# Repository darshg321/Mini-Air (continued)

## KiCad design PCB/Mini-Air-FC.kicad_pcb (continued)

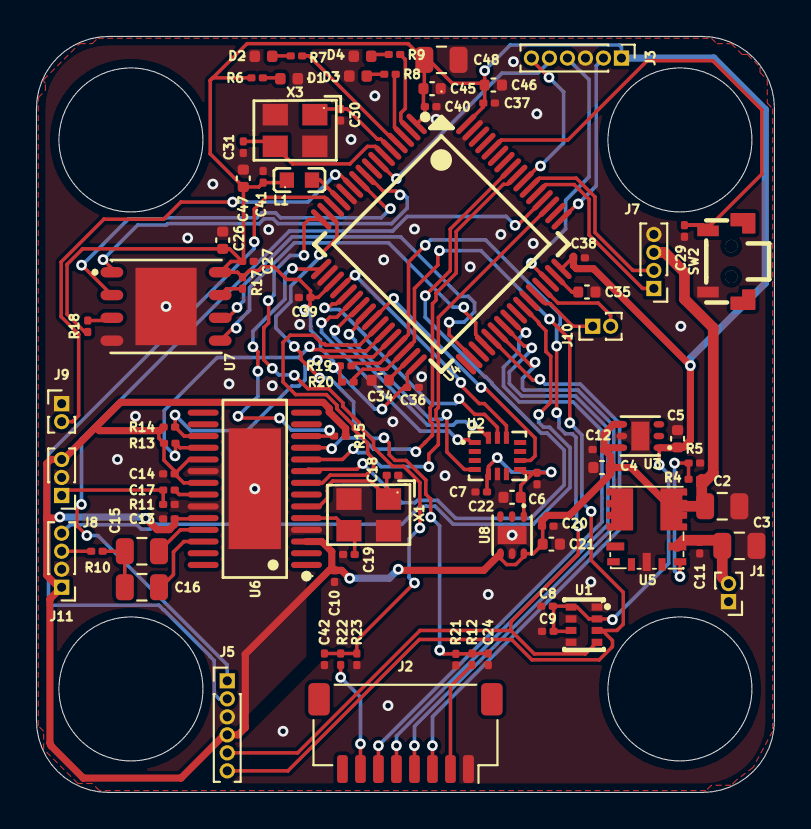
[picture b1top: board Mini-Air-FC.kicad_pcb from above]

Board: 2 copper layers, 41.0 x 42.0 mm, 84 parts (0 on the bottom side), 68 nets.

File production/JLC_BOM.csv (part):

"JLCPCB BOM Tool - BOM Matching","","","","","","","","","","","","","","","","",""
"BOM name：production_bom-JLCPCB Assembly Order.xlsx","","","Download Time：2026-06-21 03:50:59","","","","* Our matching results are updated in real-time, but stock and prices may change. 
If it's been over 24 hours, please re-match before placing your order.","","","","","","","","","",""
"PCB Assembled Qty：5","","","Est. Total Price：83.5555","","","","","","","","","","","","","",""
"Your BOM","","","","","Matched Parts","","","","","","","Order Information","","","","",""
"Top Designator","Bottom Designator","Comment","Footprint","JLCPCB Part #","Matches","Part # ","Manufacturer","Footprint","Description","Category","Warning","JLCPCB Part #","Product link","Lib Type","Qty","Source","Total Price ($)"
"C10,C11,C12,C13,C14,C17,C21,C24,C27,C29,C36,C37,C38,C39,C40,C41,C42,C6,C7,C8,C9","","100nF","0201","","Select by Customer","GRM033R61E104KE14D","Murata Electronics","0201","100nF 25V X5R ±10% 0201 Multilayer Ceramic Capacitors MLCC - SMD/SMT ROHS","Multilayer Ceramic Capacitors MLCC - SMD/SMT","","C76939","https://jlcpcb.com/partdetail/MurataElectronics-GRM033R61E10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","Extended","54","54 JLCPCB","0.6102"
"C15,C16,C2,C3","","22uF","0805","","Select by System","CL21A226MAQNNNE","Samsung Electro-Mechanics","0805","22uF 25V X5R ±20% 0805 Multilayer Ceramic Capacitors MLCC - SMD/SMT ROHS","Multilayer Ceramic Capacitors MLCC - SMD/SMT","","C45783","https://jlcpcb.com/partdetail/46786-CL21A226MAQNNNE/C45783","Basic","16","16 JLCPCB","1.8784"
"C18,C19","","22pF","0201","","Select by Customer","GRM0335C1H220JA01D","Murata Electronics","0201","22pF 50V C0G ±5% 0201 Multilayer Ceramic Capacitors MLCC - SMD/SMT ROHS","Multilayer Ceramic Capacitors MLCC - SMD/SMT","","C76924","https://jlcpcb.com/partdetail/MurataElectronics-GRM0335C1H22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","Extended","20","20 JLCPCB","0.066"
"C20,C22,C26,C4,C45,C46,C47,C5","","1uF","0402","","Select by System","CL05A105KA5NQNC","Samsung Electro-Mechanics","0402","1uF 25V X5R ±10% 0402 Multilayer Ceramic Capacitors MLCC - SMD/SMT ROHS","Multilayer Ceramic Capacitors MLCC - SMD/SMT","","C52923","https://jlcpcb.com/partdetail/53938-CL05A105KA5NQNC/C52923","Basic","26","26 JLCPCB","0.4056"
"C30,C31","","18pF","0201","","Select by System","0201CG180J500NT","FH (Guangdong Fenghua Advanced Tech)","0201","18pF 50V C0G ±5% 0201 Multilayer Ceramic Capacitors MLCC - SMD/SMT ROHS","Multilayer Ceramic Capacitors MLCC - SMD/SMT","","C62164","https://jlcpcb.com/partdetail/63221-0201CG180J500NT/C62164","Extended","20","20 JLCPCB","0.028"
"C34,C35","","2.2uF","0402","","Select by Customer","GRM155R61E225ME15D","Murata Electronics","0402","2.2uF 25V X5R ±20% 0402 Multilayer Ceramic Capacitors MLCC - SMD/SMT ROHS","Multilayer Ceramic Capacitors MLCC - SMD/SMT","","C72203","https://jlcpcb.com/partdetail/MurataElectronics-GRM155R61E22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","Extended","8","8 JLCPCB","0.3792"
"C48","","10uF","0805","","Select by System","GRM21BR61H106KE43L","Murata Electronics","0805","10uF 50V X5R ±10% 0805 Multilayer Ceramic Capacitors MLCC - SMD/SMT ROHS","Multilayer Ceramic Capacitors MLCC - SMD/SMT","","C440198","https://jlcpcb.com/partdetail/439567-GRM21BR61H106KE43L/C440198","Basic","5","5 JLCPCB","1.053"
"D1,D2,D3,D4","","LED","0402","","Select by Customer","XL-1005UGC","XINGLIGHT","0402","-40℃~+85℃ 120° 249mcd 25mA 3V 516nm~531nm 531nm 80mW Discrete Diode Emerald Green Top-mount Water Clear 0402 LED Indication - Discrete ROHS","LED Indication - Discrete","1.The comment (XL-1005UGC) of this part does not match the one (LED) provided in your BOM. Please confirm;","C965793","https://jlcpcb.com/partdetail/XINGLIGHT-XL1005UGC/C965793","Extended","20","20 JLCPCB","0.16"
"L1","","FCM1608KF-601T03","L0603","","Select by System","FCM1608KF-601T03","TAI-TECH","0603","-55℃~+125℃ 1 350mA 500mΩ 600Ω@100MHz ±25% 0603 Ferrite Beads ROHS","Ferrite Beads","","C141723","https://jlcpcb.com/partdetail/TAITECH-FCM1608KF601T03/C141723","Extended","20","20 JLCPCB","0.202"
"R5","","1.37K","0201","","Select by Customer","RTT011371FTH","RALEC","0201","-55℃~+125℃ 1.37kΩ 25V 50mW Thick Film Resistor ±1% ±200ppm/℃ 0201 Chip Resistor - Surface Mount ROHS","Chip Resistor - Surface Mount","1.The comment (RTT011371FTH) of this part does not match the one (1.37K) provided in your BOM. Please confirm;","C166356","https://jlcpcb.com/partdetail/RALEC-RTT011371FTH/C166356","Extended","20","20 JLCPCB","0.028"
"R6,R7,R8,R9","","500","0201","","Select by Customer","RC0201FR-07499RL","YAGEO","0201","-55℃~+125℃ 25V 499Ω 50mW Thick Film Resistor ±1% ±200ppm/℃ 0201 Chip Resistor - Surface Mount ROHS","Chip Resistor - Surface Mount","1.The comment (RC0201FR-07499RL) of this part does not match the one (500) provided in your BOM. Please confirm;","C138137","https://jlcpcb.com/partdetail/YAGEO-RC0201FR07499RL/C138137","Extended","20","20 JLCPCB","0.022"
"R10,R11","","75","0201","","Select by Customer","AC0201FR-0775RL","YAGEO","0201","-55℃~+155℃ 25V 50mW 75Ω Thick Film Resistor ±1% ±200ppm/℃ 0201 Chip Resistor - Surface Mount ROHS","Chip Resistor - Surface Mount","1.The comment (AC0201FR-0775RL) of this part does not match the one (75) provided in your BOM. Please confirm;","C226616","https://jlcpcb.com/partdetail/YAGEO-AC0201FR0775RL/C226616","Extended","20","20 JLCPCB","0.04"
"R12,R22","","100K","0201","","Select by Customer","RTT011003FTH","RALEC","0201","-55℃~+125℃ 100kΩ 25V 50mW Thick Film Resistor ±1% ±200ppm/℃ 0201 Chip Resistor - Surface Mount ROHS","Chip Resistor - Surface Mount","1.The comment (RTT011003FTH) of this part does not match the one (100K) provided in your BOM. Please confirm;","C102685","https://jlcpcb.com/partdetail/RALEC-RTT011003FTH/C102685","Extended","20","20 JLCPCB","0.02"
"R13,R14,R15","","1K","0201","","Select by Customer","RC0201FR-071KL","YAGEO","0201","-55℃~+125℃ 1kΩ 25V 50mW Thick Film Resistor ±1% ±200ppm/℃ 0201 Chip Resistor - Surface Mount ROHS","Chip Resistor - Surface Mount","1.The comment (RC0201FR-071KL) of this part does not match the one (1K) provided in your BOM. Please confirm;","C138165","https://jlcpcb.com/partdetail/YAGEO-RC0201FR071KL/C138165","Extended","20","20 JLCPCB","0.022"
"R17,R18,R19,R20,R4","","10K","0201","","Select by Customer","RC0201JR-0710KL","YAGEO","0201","-55℃~+125℃ 10kΩ 25V 50mW Thick Film Resistor ±200ppm/℃ ±5% 0201 Chip Resistor - Surface Mount ROHS","Chip Resistor - Surface Mount","1.The comment (RC0201JR-0710KL) of this part does not match the one (10K) provided in your BOM. Please confirm;","C138117","https://jlcpcb.com/partdetail/YAGEO-RC0201JR0710KL/C138117","Extended","20","20 JLCPCB","0.02"
"R21,R23","","47K","0201","","Select by Customer","RC0201FR-0747KL","YAGEO","0201","-55℃~+125℃ 25V 47kΩ 50mW Thick Film Resistor ±1% ±200ppm/℃ 0201 Chip Resistor - Surface Mount ROHS","Chip Resistor - Surface Mount","1.The comment (RC0201FR-0747KL) of this part does not match the one (47K) provided in your BOM. Please confirm;","C138139","https://jlcpcb.com/partdetail/YAGEO-RC0201FR0747KL/C138139","Extended","20","20 JLCPCB","0.022"
"SW2","","TS24CA","SW-SMD_2P-TS24CA","","Select by System","TS24CA","SHOU HAN","SMD,4.6x1.8mm","-20℃~+70℃ 1.6N 1.9mm 12V 20,000 cycles 3.5mm 4.7mm 50mA Black No Rectangular Button SMD(SMT) Tab SPST Surface Mount, Right Angle Without Bracket SMD,4.6x1.8mm Tactile Switches ROHS","Tactile Switches","","C393942","https://jlcpcb.com/partdetail/SHOUHAN-TS24CA/C393942","Extended","7","7 JLCPCB","0.175"
"U1","","BMP280","LGA-8_L2.5-W2.0-P0.65_AMP6127","","Select by System","BMP280","Bosch Sensortec","LGA-8(2x2.5)","-40℃~+85℃ 0.12hpa 1.5pa/K 1.71V~3.6V 1hpa 300nA 30Kpa~1.1bar I2C、SPI LGA-8(2x2.5) Pressure Sensors ROHS","Pressure Sensors","","C83291","https://jlcpcb.com/partdetail/BoschSensortec-BMP280/C83291","Extended","2","2 JLCPCB","13.7058"
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
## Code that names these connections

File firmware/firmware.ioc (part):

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Mcu.Name=STM32F405RGTx
Mcu.Package=LQFP64
Mcu.UserName=STM32F405RGTx
PA0-WKUP.GPIOParameters=GPIO_Label
PA0-WKUP.GPIO_Label=GPS_RX
PA0-WKUP.Mode=Asynchronous
PA0-WKUP.Signal=UART4_TX
PA1.GPIOParameters=GPIO_Label
PA1.GPIO_Label=ADC_V_ESC
PA1.Signal=ADCx_IN1
PA10.Mode=Asynchronous
PA10.Signal=USART1_RX
PA11.GPIOParameters=GPIO_Label
PA11.GPIO_Label=TEST_OUT
PA11.Signal=GPIO_Output
PA12.GPIOParameters=GPIO_Label
PA12.GPIO_Label=TEST_IN
PA12.Signal=GPIO_Input
PA13.GPIOParameters=GPIO_Label
PA13.GPIO_Label=SWDIO
PA13.Mode=Trace_Asynchronous_SW
PA13.Signal=SYS_JTMS-SWDIO
PA14.GPIOParameters=GPIO_Label
PA14.GPIO_Label=SWCLK
PA14.Mode=Trace_Asynchronous_SW
PA14.Signal=SYS_JTCK-SWCLK
PA2.GPIOParameters=GPIO_Label
PA2.GPIO_Label=ADC_C_ESC
PA2.Signal=ADCx_IN2
PA3.GPIOParameters=GPIO_Label
PA3.GPIO_Label=OSD_LOS
PA3.Signal=GPIO_Input
PA4.GPIOParameters=GPIO_Label
PA4.GPIO_Label=ICM_CS
PA4.Signal=GPIO_Output
PA5.GPIOParameters=GPIO_Label
PA5.GPIO_Label=ICM_SCK
PA5.Mode=Full_Duplex_Master
PA5.Signal=SPI1_SCK
PA6.GPIOParameters=GPIO_Label
PA6.GPIO_Label=ICM_SDO
PA6.Mode=Full_Duplex_Master
PA6.Signal=SPI1_MISO
PA7.GPIOParameters=GPIO_Label
PA7.GPIO_Label=ICM_SDI
PA7.Mode=Full_Duplex_Master
PA7.Signal=SPI1_MOSI
PA9.GPIOParameters=GPIO_Label
PA9.GPIO_Label=VTX_RX
PA9.Mode=Asynchronous
PA9.Signal=USART1_TX
PB0.GPIOParameters=GPIO_Label
PB0.GPIO_Label=OSD_CS
PB0.Signal=GPIO_Output
PB1.GPIOParameters=GPIO_Label
PB1.GPIO_Label=OSD_HSYNC
PB1.Signal=GPIO_Input
PB10.GPIOParameters=GPIO_Label
PB10.GPIO_Label=SCL
PB10.Mode=I2C
PB10.Signal=I2C2_SCL
PB11.GPIOParameters=GPIO_Label
PB11.GPIO_Label=SDA
PB11.Mode=I2C
PB11.Signal=I2C2_SDA
PB13.GPIOParameters=GPIO_Label
PB13.GPIO_Label=MEM_SCK
PB13.Mode=Full_Duplex_Master
PB13.Signal=SPI2_SCK
PB15.GPIOParameters=GPIO_Label
PB15.GPIO_Label=MEM_SDI
PB15.Mode=Full_Duplex_Master
PB15.Signal=SPI2_MOSI
PB2.GPIOParameters=GPIO_Label
PB2.GPIO_Label=OSD_VSYNC
PB2.Signal=GPIO_Input
PB3.GPIOParameters=GPIO_Label
PB3.GPIO_Label=SWO
PB3.Mode=Trace_Asynchronous_SW
PB3.Signal=SYS_JTDO-SWO
PB4.GPIOParameters=GPIO_Label
PB4.GPIO_Label=OSD_SDO
PB4.Mode=Full_Duplex_Master
PB4.Signal=SPI3_MISO
PB5.GPIOParameters=GPIO_Label
PB5.GPIO_Label=OSD_SDI
PB5.Mode=Full_Duplex_Master
PB5.Signal=SPI3_MOSI
PC1.GPIOParameters=GPIO_Label
PC1.GPIO_Label=MEM_CS
PC1.Signal=GPIO_Output
PC10.GPIOParameters=GPIO_Label
PC10.GPIO_Label=OSD_SCK
PC10.Mode=Full_Duplex_Master
PC10.Signal=SPI3_SCK
PC11.GPIOParameters=GPIO_Label
PC11.GPIO_Label=GPS_TX
PC11.Mode=Asynchronous
PC11.Signal=UART4_RX
PC12.GPIOParameters=GPIO_Label
PC12.GPIO_Label=RECEIVER_RX
PC12.Mode=Asynchronous
PC12.Signal=UART5_TX
PC13-ANTI_TAMP.GPIOParameters=GPIO_Label
PC13-ANTI_TAMP.GPIO_Label=LED3
PC13-ANTI_TAMP.Signal=GPIO_Output
PC14-OSC32_IN.GPIOParameters=GPIO_Label
PC14-OSC32_IN.GPIO_Label=LED2
PC14-OSC32_IN.Signal=GPIO_Output
PC15-OSC32_OUT.GPIOParameters=GPIO_Label
PC15-OSC32_OUT.GPIO_Label=LED1
PC15-OSC32_OUT.Signal=GPIO_Output
PC2.GPIOParameters=GPIO_Label
PC2.GPIO_Label=MEM_SDO
PC2.Mode=Full_Duplex_Master
PC2.Signal=SPI2_MISO
PC3.GPIOParameters=GPIO_Label
PC3.GPIO_Label=CAM_CTRL
PC3.Signal=GPIO_Output
PC4.GPIOParameters=GPIO_Label
PC4.GPIO_Label=ICM_INT1
PC4.Signal=GPXTI4
PC5.GPIOParameters=GPIO_Label
PC5.GPIO_Label=ICM_INT2
PC5.Signal=GPXTI5
PC6.GPIOParameters=GPIO_Label
PC6.GPIO_Label=MTR1
PC6.Signal=S_TIM8_CH1
PC7.GPIOParameters=GPIO_Label
PC7.GPIO_Label=MTR2
PC7.Signal=S_TIM8_CH2
PC8.GPIOParameters=GPIO_Label
PC8.GPIO_Label=MTR3
PC8.Signal=S_TIM8_CH3
PC9.GPIOParameters=GPIO_Label
PC9.GPIO_Label=MTR4
PC9.Signal=S_TIM8_CH4
PD2.GPIOParameters=GPIO_Label
PD2.GPIO_Label=RECEIVER_TX
PD2.Mode=Asynchronous
PD2.Signal=UART5_RX
PH0-OSC_IN.GPIOParameters=GPIO_Label
PH0-OSC_IN.GPIO_Label=HSE_IN
PH0-OSC_IN.Mode=HSE-External-Oscillator
PH0-OSC_IN.Signal=RCC_OSC_IN
PH1-OSC_OUT.GPIOParameters=GPIO_Label
PH1-OSC_OUT.GPIO_Label=HSE_OUT
PH1-OSC_OUT.Mode=HSE-External-Oscillator
PH1-OSC_OUT.Signal=RCC_OSC_OUT
RCC.HSE_VALUE=25000000
RCC.SYSCLKFreq_VALUE=16000000
board=custom

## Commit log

2026-06-21 done!
2026-06-26 clarification
2026-06-26 edited cad
2026-06-27 improved
